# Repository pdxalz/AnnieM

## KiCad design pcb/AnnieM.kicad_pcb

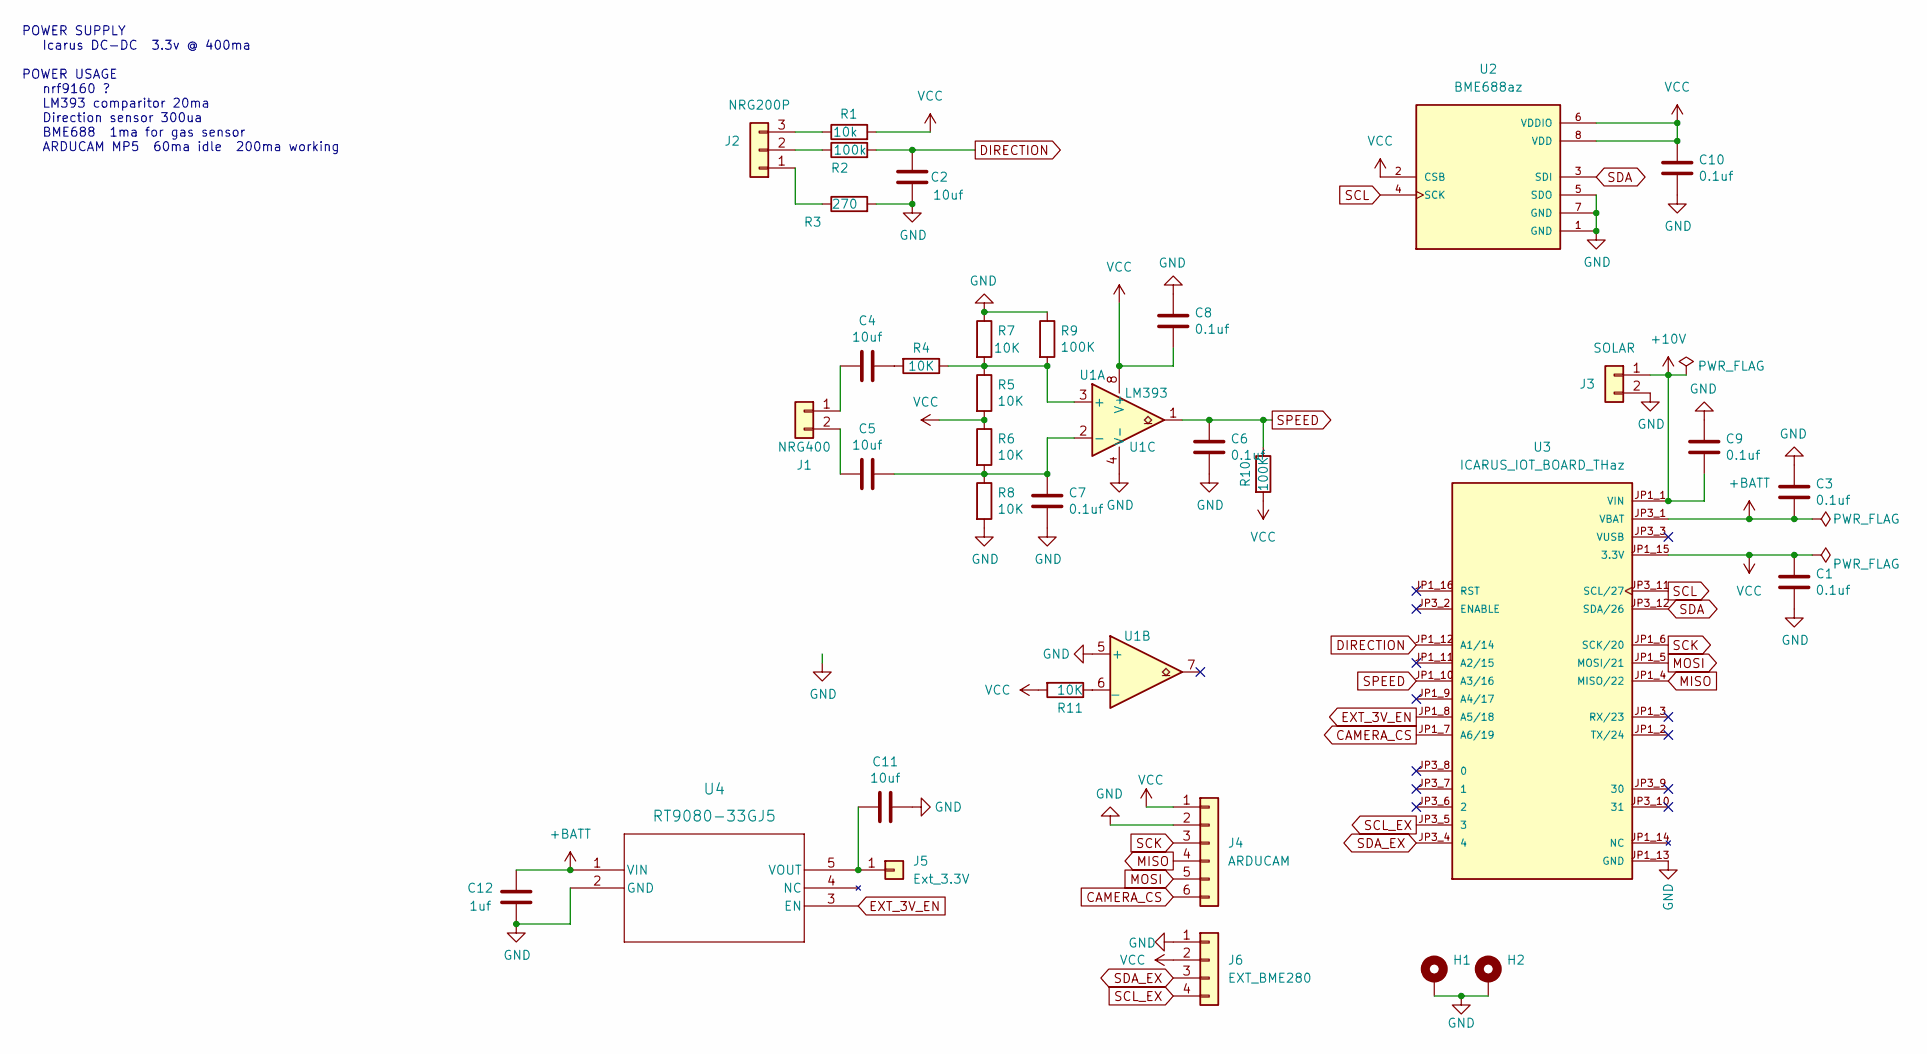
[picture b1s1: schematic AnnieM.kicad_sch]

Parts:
C1, C3, C6, C7, C8, C9, C10: 0.1uf; C_0603_1608Metric
C2, C4, C5, C11: 10uf; C_0805_2012Metric
C12: 1uf; C_0805_2012Metric
H1, H2: MountingHole_2.2mm_M2_DIN965_Pad
J1: NRG400; TerminalBlock_RND_205-00232_1x02_P5.08mm_Horizontal
J2: NRG200P; TerminalBlock_RND_205-00233_1x03_P5.08mm_Horizontal
J3: SOLAR; JST_XA_B02B-XASK-1_1x02_P2.50mm_Vertical
J4: ARDUCAM; PinHeader_1x06_P2.54mm_Vertical
J5: Ext_3.3V; PinSocket_1x01_P2.54mm_Vertical
J6: EXT_BME280; PinSocket_1x04_P2.54mm_Vertical
R1: 10k; R_0603_1608Metric
R2: 100k; R_0603_1608Metric
R3: 270; R_0603_1608Metric
R4, R5, R6, R7, R8, R11: 10K; R_0603_1608Metric
R9, R10: 100K; R_0603_1608Metric
U1: LM393; DIP-8_W7.62mm_LongPads
U2: BME688az; IC_BME688; PARTREV 1.0
U3: ICARUS_IOT_BOARD_THaz; MODULE_ICARUS_IOT_BOARD_THaz; PARTREV January 20, 2020
U4: RT9080-33GJ5; TSOT-23-5

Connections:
+10V: C9.1, J3.1, U3.JP1_1 (VIN)
+BATT: C3.1, C12.1, U3.JP3_1 (VBAT), U4.1 (VIN)
CAMERA_CS: J4.6, U3.JP1_7 (A6/19)
DIRECTION: C2.2, R2.2, U3.JP1_12 (A1/14)
EXT_3V_EN: U3.JP1_8 (A5/18), U4.3 (EN)
GND: C1.1, C2.1, C3.2, C6.1, C7.1, C8.2, C9.2, C10.1, C11.1, C12.2, H1.1, H2.1, J3.2, J4.2, J6.1, R3.2, R7.1, R8.2, R9.1, U1.4 (V-), U1.5 (+), U2.1 (GND), U2.5 (SDO), U2.7 (GND), U3.JP1_13 (GND), U4.2 (GND)
MISO: J4.4, U3.JP1_4 (MISO/22)
MOSI: J4.5, U3.JP1_5 (MOSI/21)
unnamed: C4.1, R4.2
unnamed: C4.2, J1.1
unnamed: C5.1, C7.2, R6.2, R8.1, U1.2 (-)
unnamed: C5.2, J1.2
unnamed: C11.2, J5.1, U4.5 (VOUT)
unnamed: J2.1, R3.1
unnamed: J2.2, R2.1
unnamed: J2.3, R1.1
unnamed: R4.1, R5.1, R7.2, R9.2, U1.3 (+)
unnamed: R11.1, U1.6 (_)
SCK: J4.3, U3.JP1_6 (SCK/20)
SCL: U2.4 (SCK), U3.JP3_11 (SCL/27)
SCL_EX: J6.4, U3.JP3_5 (3)
SDA: U2.3 (SDI), U3.JP3_12 (SDA/26)
SDA_EX: J6.3, U3.JP3_4 (4)
SPEED: C6.2, R10.1, U1.1, U3.JP1_10 (A3/16)
VCC: C1.2, C8.1, C10.2, J4.1, J6.2, R1.2, R5.2, R6.1, R10.2, R11.2, U1.8 (V+), U2.2 (CSB), U2.6 (VDDIO), U2.8 (VDD), U3.JP1_15 (3.3V)

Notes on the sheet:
POWER SUPPLY Icarus DC-DC 3.3v @ 400ma POWER USAGE nrf9160 ? LM393 comparitor 20ma Direction sensor 300ua BME688 1ma for gas sensor ARDUCAM MP5 60ma idle 200ma working

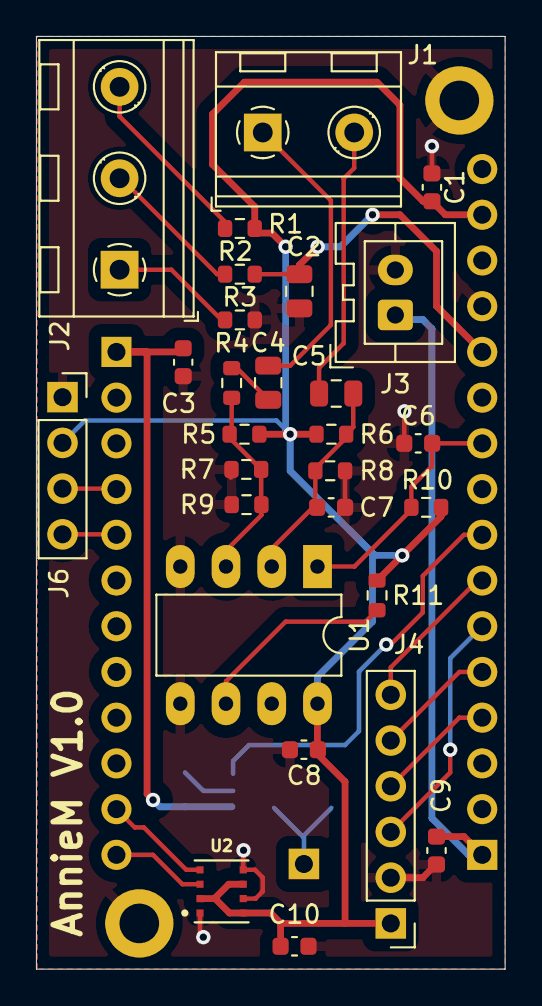
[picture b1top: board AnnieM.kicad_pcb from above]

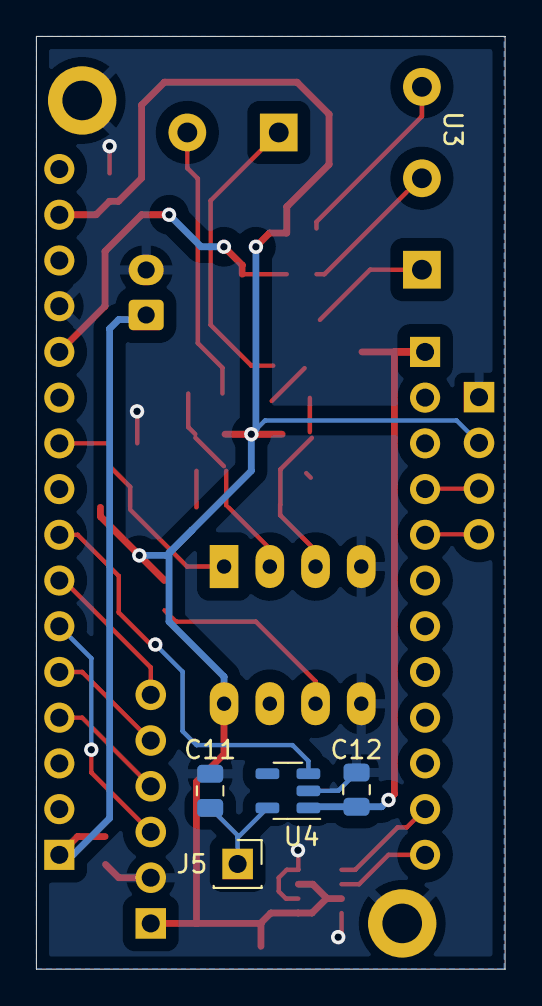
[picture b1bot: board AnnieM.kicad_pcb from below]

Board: 2 copper layers, 26.0 x 51.8 mm, 35 parts (5 on the bottom side), 25 nets.

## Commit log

2023-05-10 Initial revision. Windspeed sensor connected to GPIO-10, reporting to Log.
2023-05-10 Added wind_sensor module
2023-05-11 two timers
2023-05-13 Sending speed data to mqtt broker
2023-05-18 Added retain flag to publish function
2023-05-20 added timer for sensor check, actual time, power ctrl
2023-05-24 cleared history at boot, cleaned msg format, added cmds, changed broker
2023-05-24 cleaned up warnings
2023-05-26 cleaned up message topics
2023-05-26 Added battery check message
2023-06-01 Added power reading
2023-06-06 Add cmd to ask for a report and 12 health samples,
2023-06-07 Added temperature module
2023-06-08 added adc code, working
2023-06-15 Fixed direction calculation
2023-06-16 working system with speed, dir, and health
2023-06-18 Temp working and F, code organizing
2023-06-20 fixed format on json string
2023-06-22 working on power management
2023-06-24 Added recent data and minor formatting stuff
2023-06-24 Added recent data
2023-06-24 Create CNAME
2023-06-25 added disclaimer
2023-06-25 spelling error
2023-06-29 Readable wind direction and reordered wind table
2023-07-06 dead sensor message
2023-07-14 Icarus sending mqtt
2023-07-22 Speed, Dir, & voltage working
2023-07-25 Added PCB files
2023-07-26 added health module
2023-08-01 added pull up to schematic
2023-08-01 Temperature adc is working, fixed adc code.
2023-08-12 added graph (kind of working)
2023-08-13 chart changes, not great
2023-08-14 Minor changes for power consumption
2023-08-17 msg to Jason
2023-08-18 graph ends at current time
2023-08-18 Display only last six hours
2023-08-18 only showing last two hours
2023-08-19 plot data since 12am
2023-08-19 Added direction plot and more data
2023-08-20 added horizontal scrolling
2023-08-20 updated message
2023-08-20 starts scrolled to the right
2023-08-20 Code cleanup, diplaying 12 hour time
2023-08-20 NWSE scales, in blue
2023-08-20 inital header changes
2023-08-21 Fixed missing labels and display width
2023-08-21 detecting corrupted data, fixed direction scale.
2023-08-21 testing phone issue
2023-08-21 phone test
2023-08-21 phone testing
2023-08-21 adding panels
2023-08-22 font sizes
2023-08-22 Lior's UX changes, also spelling errors.
2023-08-23 lager size for current wind
2023-08-23 code clean up
2023-08-23 Added donate, moved text, changed label size
2023-08-25 Added gusts and + to direction offset
2023-08-28 added workspace
2023-09-02 Fixed 2 code errors, added + to direction,
2023-09-02 season end message
2023-12-07 refresh file
2023-12-08 Annie External Sim, SDK 2.2 fixed build issues.
2023-12-08 Restarted pcb layout, added bme866 and Arducam 5MP
2023-12-10 Changed LED status
2023-12-13 Using Logging system, printing published data.
2023-12-14 relayout, new temp and camera connection
2023-12-14 Reordered annotations graphically
2023-12-17 Fixed time issues, removed unneeded recent message
2023-12-17 fixed recent direction string
2023-12-19 reorganized and renamed wind sensor timers and routines
2023-12-19 reorganized health.c
2023-12-19 reorganized mqtt_connection
2023-12-21 cleaned up buffer usage, possible buffer overflow fix
2023-12-23 changed board area to be 2"
2023-12-24 Added gust and lulls. Reports every 10 minutes.
2023-12-28 Minor changes, Sent off to OSHPark
2023-12-28 modified overlay to fix conflicts
2024-01-03 Changed to HiveMQ Broker
2024-01-11 Add second chart to test fastapi. local host only.
2024-01-11 Remove MQTT stuff and first chart
2024-01-11 Send current wind only.
2024-01-27 made data order consistant, shorten time msg, fixed avg bug
2024-02-23 Added camera code. Working out serial port.
2024-02-28 Increased stack and mem pool, attempts at fixing mem issue. Works but not reliably.
2024-03-02 Camera code suddenly working great. Don't know why.
2024-03-13 Added commands for serial photo and hacks to hide corruption issues. Working ok, but large images get corrupted
2024-03-18 Added external power control
2024-03-19 Camera power on only for image capture.
2024-03-19 Reduced delays and increased buffer for semi reliable captures.
2024-04-04 Added watchdog, signal strength. Still has picture hang on weak signal.
2024-04-12 fixed health not updating issue, set reports to 6 per hour, changed watchdog to less often, fixed minor debug issue,
2024-04-30 Changes before installing sensor (I think). Added temperature and pressure to the health status. Also tried to improve camera reliability.
2024-05-01 Added reset command z!, and added humidity to health report.
2024-05-02 Move direction ADC input to A2, removed obsolete temperature adc
2024-05-02 Moved windspeed to PIO_1.2, pin JP3-6
2024-05-03 Fixed photo send bug. Still has timeout issue.
2024-05-10 added commands, h-health, l-led,
2024-05-12 added image commands for exposure, focus, sharpness and quality.
2024-11-04 Added camera support code, minor camera tweaks.
2025-04-06 switched to personal mqtt broker
